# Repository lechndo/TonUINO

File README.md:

**THIS IS A FORK OF https://github.com/seisfeld/TonUINO!
unfortunately github can't handle forks of forks (with same name).**  

Alternative TonUINO Firmware
============================

Dies ist meine alternative Firmware für das wundervolle [TonUINO](https://www.voss.earth/tonuino/) Projekt. Ziel ist hier nicht unbedingt 100%ige Funktionsgleichheit mit der original Firmware. Es wurden vielmehr für meinen Zweck interessante Funktionen hinzugefügt und desweiteren auch einige Punkte (erstmal?) ausgelassen. Im großen und ganzen macht es einfach Spaß, sich mit der TonUINO Plattform auszutoben, ich bin deswegen auch viel in der [TonUINO Community](https://discourse.voss.earth/) aktiv. Schaut doch einfach mal vorbei - ihr findet dort viele Bauvorschläge, Hacks und Informationen rund um den TonUINO.

**Die Firmware wird "as-is" zur Verfügung gestellt. Wenn jemand die Firmware in seinem TonUINO einsetzt, freue ich mich natürlich darüber. Ich kann allerdings keinen Support bieten.**

## Inhalt
- [Funktionsübersicht](https://github.com/seisfeld/TonUINO#funktionsübersicht)
- [Tastenbelegung](https://github.com/seisfeld/TonUINO#tastenbelegung)
- [PIN Code](https://github.com/seisfeld/TonUINO#pin-code)
- [Ordnerstruktur auf der SD Karte](https://github.com/seisfeld/TonUINO#ordnerstruktur-auf-der-sd-karte)
- [Audio Meldungen](https://github.com/seisfeld/TonUINO#audio-meldungen)
  - [Audio Meldungen herunterladen](https://github.com/seisfeld/TonUINO#audio-meldungen-herunterladen)
  - [Audio Meldungen selbst erzeugen](https://github.com/seisfeld/TonUINO#audio-meldungen-selbst-erzeugen)
      - [Audio Meldungen mit say und ffmpeg erzeugen](https://github.com/seisfeld/TonUINO#audio-meldungen-mit-say-und-ffmpeg-erzeugen)
      - [Audio Meldungen mit Amazon Polly erzeugen](https://github.com/seisfeld/TonUINO#audio-meldungen-mit-amazon-polly-erzeugen)
      - [Audio Meldungen mit dem Cloud text-to-speech Service von Google erzeugen](https://github.com/seisfeld/TonUINO#audio-meldungen-mit-dem-cloud-text-to-speech-service-von-google-erzeugen)
      - [Hilfe und weitere Optionen](https://github.com/seisfeld/TonUINO#hilfe-und-weitere-optionen)
- [Titelansagen in MP3-Dateien einfügen](https://github.com/seisfeld/TonUINO#titelansagen-in-mp3-dateien-einfügen)
  - [Funktionsweise](https://github.com/seisfeld/TonUINO#funktionsweise)
  - [Hilfe und weitere Optionen](https://github.com/seisfeld/TonUINO#hilfe-und-weitere-optionen-1)
- [Lizenz](https://github.com/seisfeld/TonUINO#lizenz)

## Funktionsübersicht

- Standard Abspielmodi: Hörspiel, Album, Party, Lieblingsfolge und Hörbuch.
- Erweiterte Abspielmodi: Virtuelle Ordner für die Modi Hörspiel, Album und Party.
- Nächster/Vorheriger Titel sowohl in den Standard Abspielmodi Album, Party und Hörbuch - als auch bei der Nutzung von virtuellen Ordnern in den Modi Album und Party.
- Der aktuell laufende Titel kann dauerhaft wiederholt werden.
- Speichert die Ordnerverknüpfungen, Abspielmodi etc. auf den NFC Tags/Karten.
- Unterstützung für MIFARE Classic (Mini, 1K & 4K) Tags/Karten.
- Unterstützung für MIFARE Ultralight / Ultralight C Tags/Karten.
- Unterstützung für NTAG213/215/216 Tags/Karten.
- Debugausgabe auf der seriellen Konsole.
- Einstellungen werden im EEPROM gespeichert.
- Konfigurationsdialoge (NFC Tags/Karten anlernen/löschen, Elternmenü etc.) können abgebrochen werden.
- NFC Tags/Karten können wieder komplett gelöscht werden.
- Elternmenü um NFC Tags/Karten zu löschen und um Einstellungen wie Startlautstärke, Maximallautstärke, Menülautstärke, Equalizer und Abschalttimer (benötigt eine externe Schaltung oder eine passende Powerbank) vorzunehmen. Dort kann TonUINO auch von Hand abgeschaltet werden und es lassen sich der Hörbuchfortschritt und die Einstellugen zurücksetzen.
- **Optional:** PIN Code um Elternfunktionen zu schützen.
- **Optional:** Umstellbar auf 5 Tasten Bedienung.
- **Optional:** Fernbedienbar über eine Infrarotfernbedienung (diese muss mindestens 7 Tasten haben), welche über das Elternmenü angelernt werden kann. Über die Fernbedienung ist es dann auch möglich die Tasten von TonUINO zu sperren.
- **Optional:** Unterstützung einer Status LED.
- **Optional:** Unterstützung von WS281x LED(s) als Status LED(s).
- **Optional:** Unterspannungsabschaltung für z.B. die [CubieKid Platine](https://www.thingiverse.com/thing:3148200).
- **Optional:** Unterstützung des [Pololu Power Switch (LV)](https://www.pololu.com/product/2808).

## Tastenbelegung

## PIN Code

Der (optional einschaltbare) PIN Code um die Elternfunktionen abzusichern lautet standard mässig

- `play/pause, vol-, vol+, play/pause`

und kann im Sketch vor dem kompilieren geändert werden.

## Ordnerstruktur auf der SD Karte

Die Ordner auf der SD Karte, in denen eure MP3-Dateien abgelegt werden, müssen **01 bis 99** heissen - also **zweistellig** sein. Die Dateien in den Ordnern müssen mit einer **dreistelligen** Nummer beginnen - **001 bis 255** - können aber in der Regel [1] weitere Zeichen enthalten. Erlaubt wäre demnach `001.mp3` oder auch `001Lieblingslied.mp3`.

Es hat sich bewährt, die gesammte Ordnerstruktur auf dem Comupter vorzubereiten und dann in einem Rutsch auf die SD Karte zu kopieren. So wird sichergestellt, daß alle Dateien auch in der richtigen Reihenfolge sind.

[1] Nicht alle DFPlayer Mini Module akzeptieren im Dateinamen weitere Zeichen hinter der dreistelligen Nummer. Hier geht dann leider nur `001.mp3`, `002.mp3` usw.

## Audio Meldungen

TonUINO funktioniert nur korrekt, wenn ein **zur Firmware passendes** Set an Audio Meldungen auf der SD Karte vorhanden ist. Dies sind die Ordner **advert** und **mp3**.

### Audio Meldungen herunterladen

Die Audio Meldungen sind mit Amazon Polly generiert worden und können in verschiedenen Sprachen heruntergeladen werden:

- Deutsch: [audio-messages-polly-de.zip](https://seisfeld.github.io/tonuino/audio-messages-polly-de.zip)
- Englisch: [audio-messages-polly-en.zip](https://seisfeld.github.io/tonuino/audio-messages-polly-en.zip)
- Niederländisch: [audio-messages-polly-nl.zip](https://seisfeld.github.io/tonuino/audio-messages-polly-nl.zip)

Die `.zip` Datei entpacken und die Ordner **advert** und **mp3** auf die SD Karte kopieren. Fertig.

### Audio Meldungen selbst erzeugen

Das passende Set an Audio Meldungen lässt sich auch jederzeit mit dem beigelegten Python Skript `create_audio_messages.py` erzeugen. Hier sind dann auch weitere text-to-speech Engines möglich wenn ihr möchtet (siehe unten). Das Skript kann sowohl **deutsche**, **englische** als auch **niederländische** Audio Meldungen erzeugen (unterstützt wird ebenfalls **französisch**, es liegt dafür allerdings momentan keine Quelldatei bei). Es ist unter macOS, Linux und Windows getested, und benötigt **Python 3** und ggf. **ffmpeg**.

Unter Linux kann Python 3 mit dem zur Distribution gehörenden Paketmanager installiert werden. macOS Nutzer benutzen z.B. [Homebrew](https://brew.sh): `brew install python` und für Windows kann es [hier heruntergeladen werden](https://www.python.org/downloads/windows/).

Das Skript unerstützt dabei die Nutzung von drei text-to-speech Engines:

- Lokal - nur unter macOS - mit den Tools `say` und `ffmpeg`. Sofern man einen Mac hat ist dieser Weg schnell, einfach und dauerhaft kostenlos.
- Über das Internet mit Amazon Polly, dem text-to-speech Service von Amazon.
- Über das Internet mit Hilfe des Cloud text-to-speech Service von Google.

Für die Anzahl der benötigten Meldungen ist die Nutzung der Services von Amazon ([Preise](https://aws.amazon.com/de/polly/pricing/)) bzw. Google ([Preise](https://cloud.google.com/text-to-speech/pricing)) erstmal kostenlos. Für beide Services muss man allerdings erst einen Account anlegen, ist dann das Freikontingent irgendwann einmal aufgebraucht fallen Kosten im Bereich von ein paar Cent an.

#### Audio Meldungen mit `say` und `ffmpeg` erzeugen

Neben dem Tool `say` (ist Teil von macOS) wird hier noch `ffmpeg` benötigt.

1. `ffmpeg` installieren, z.B. via [Homebrew](https://brew.sh): `brew install ffmpeg`
2. In den Ordner wechseln wo ihr die `.zip` Datei von GitHub entpackt, bzw. das Repository gecloned habt.
3. `python3 tools/create_audio_messages.py --use-say` ausführen.
4. Kopiert nun den Inhalt des Ordners **sd-card** auf die SD Karte. Fertig.

#### Audio Meldungen mit Amazon Polly erzeugen

1. Auf der [AWS](https://aws.amazon.com/) Webseite einen Account anlegen und Access Keys erzeugen.
2. Das Tool `aws` [installieren](https://docs.aws.amazon.com/de_de/cli/latest/userguide/cli-chap-install.html) (Windows / Linux), macOS z.B. via [Homebrew](https://brew.sh): `brew install awscli`.
3. Das Tool `aws` [konfigurieren](https://docs.aws.amazon.com/de_de/cli/latest/userguide/cli-chap-configure.html).
4. In den Ordner wechseln wo ihr die `.zip` Datei von GitHub entpackt, bzw. das Repository gecloned habt.
5. `python3 tools/create_audio_messages.py --use-amazon` ausführen.
6. Kopiert nun den Inhalt des Ordners **sd-card** auf die SD Karte. Fertig.

#### Audio Meldungen mit dem Cloud text-to-speech Service von Google erzeugen

1. Auf Googles [Cloud text-to-speech](https://cloud.google.com/text-to-speech/) Webseite einen Account anlegen und einen API-Key erzeugen.
2. In den Ordner wechseln wo ihr die `.zip` Datei von GitHub entpackt, bzw. das Repository gecloned habt.
3. `python3 tools/create_audio_messages.py --use-google-key=ABCD` ausführen.
4. Kopiert nun den Inhalt des Ordners **sd-card** auf die SD Karte. Fertig.

#### Hilfe und weitere Optionen

Das Python Skript hat noch einige weitere Funktionen. Eine Übersicht gibt:

- `python3 tools/create_audio_messages.py --help`

## Titelansagen in MP3-Dateien einfügen

Im Hörspielmodus gibt es das Problem, daß man beim Auflegen der Karte nicht weiß, welche Folge abgespielt wird. Spielt man z.B. *Benjamin Blümchen* ab, dann kommt immer zuerst der Titelsong, der sich bei allen Folgen gleich anhört.

Das Python Skript `add_lead_in_messages.py` fügt der MP3-Datei eine Titelansage wie z.B. *Benjamin Blümchen im Urlaub* hinzu. Wenn man eine andere Folge hören möchte, kann man dann einfach nochmal die *Benjamin Blümchen* Karte auflegen. Es ist unter macOS getested, sollte aber mit minimalem Aufwand auch unter Windows / Linux laufen - wenn alle Abhängigkeiten erfüllt werden.

### Funktionsweise

Angenommen man hat einen Ordner mit folgendem Inhalt:

```
+- 04_Benjamin Blümchen
   +- Benjamin Blümchen hat Geburtstag.mp3
   +- Benjamin Blümchen im Urlaub.mp3
   +- Benjamin Blümchen als Pilot.mp3
```

Dann kann man mit folgendem Aufruf MP3-Dateien mit Ansagen generieren (Beispiel):

    python3 tools/add_lead_in_messages.py -i '04_Benjamin Blümchen' -o /Volumes/TonUINO/04 --google-key=ABCD --add-numbering

Was dann passiert:

- Es werden neue MP3-Dateien mit den Ansagen erzeugt. Man kann dabei auch optional direkt auf die SD-Karte schreiben (wie im Beispiel).
- Die Original-Dateien werden dabei nicht geändert.
- Die MP3-Dateien werden nicht neu enkodiert (also kein Qualitätsverlust).
- Auf Wunsch werden die MP3-Dateien kompatibel zum DFPlayer Mini numeriert. Also z.B. `001_Benjamin Blümchen hat Geburtstag.mp3` (Parameter `--add-numbering`)
- Das Skript unerstützt dabei die Nutzung von drei text-to-speech Engines:
  - Lokal - nur unter macOS - mit den Tools `say` und `ffmpeg`. (Parameter `--use-say`)
  - Über das Internet mit Amazon Polly, dem text-to-speech Service von Amazon. (Parameter `--use-amazon`)
  - Über das Internet mit Hilfe des Cloud text-to-speech Service von Google. (Parameter `--google-key=ABCD`)

Das Ergebnis sieht dann so aus:

```
+- /Volumes/TonUINO/04
   +- 001_Benjamin Blümchen hat Geburtstag.mp3
   +- 002_Benjamin Blümchen im Urlaub.mp3
   +- 003_Benjamin Blümchen als Pilot.mp3
```

#### Hilfe und weitere Optionen

Das Python Skript hat noch einige weitere Funktionen. Eine Übersicht gibt:

- `python3 tools/add_lead_in_messages.py --help`

## Lizenz

GPL v3. Siehe [LICENSE](../LICENSE.md).

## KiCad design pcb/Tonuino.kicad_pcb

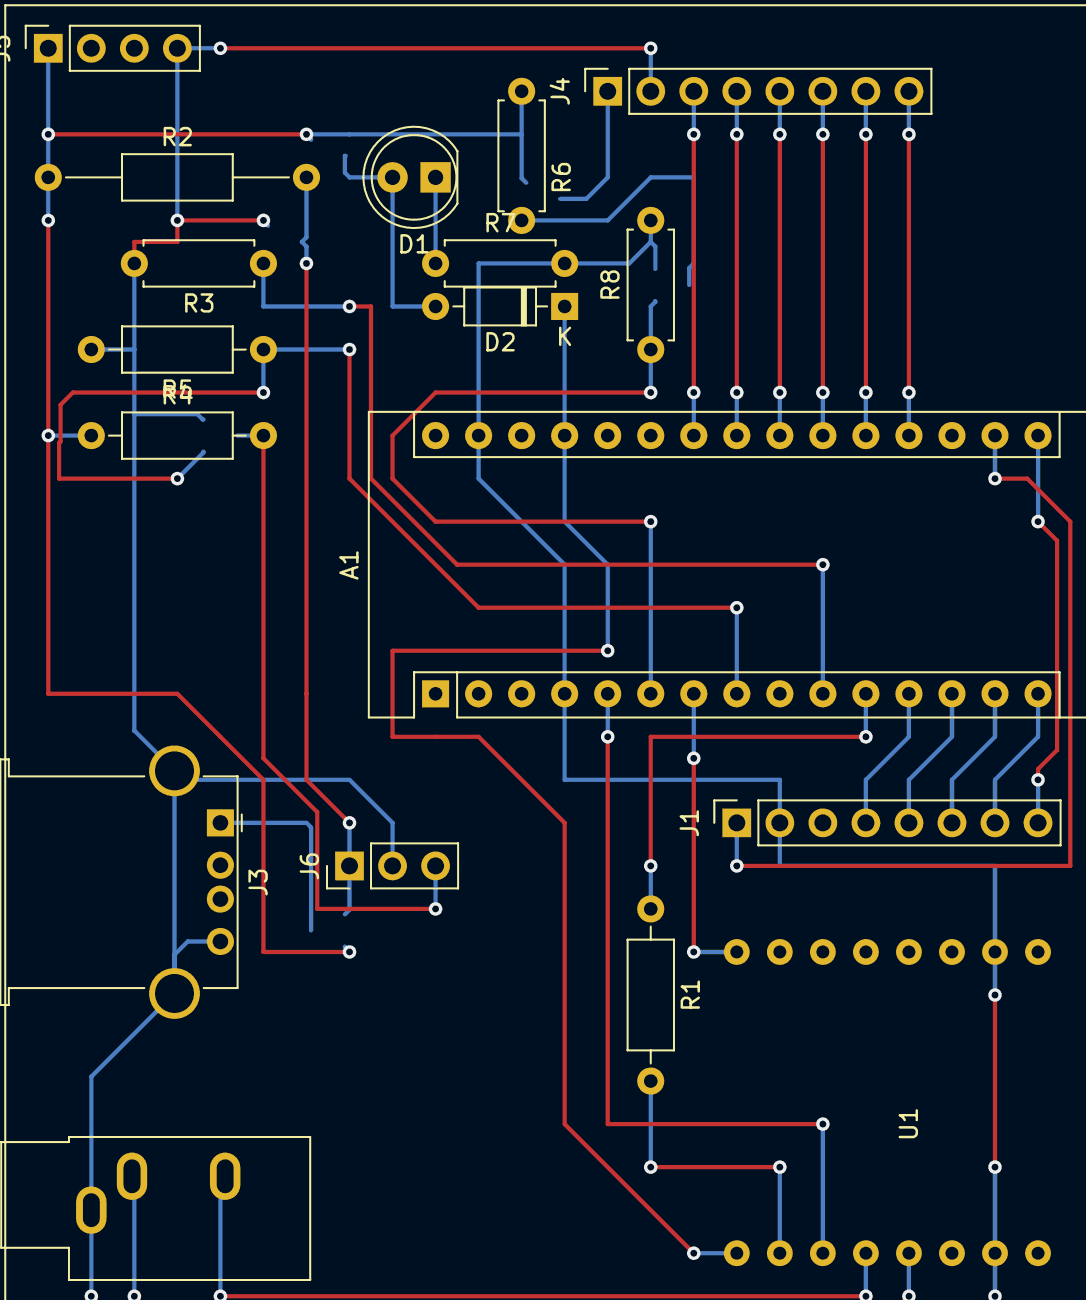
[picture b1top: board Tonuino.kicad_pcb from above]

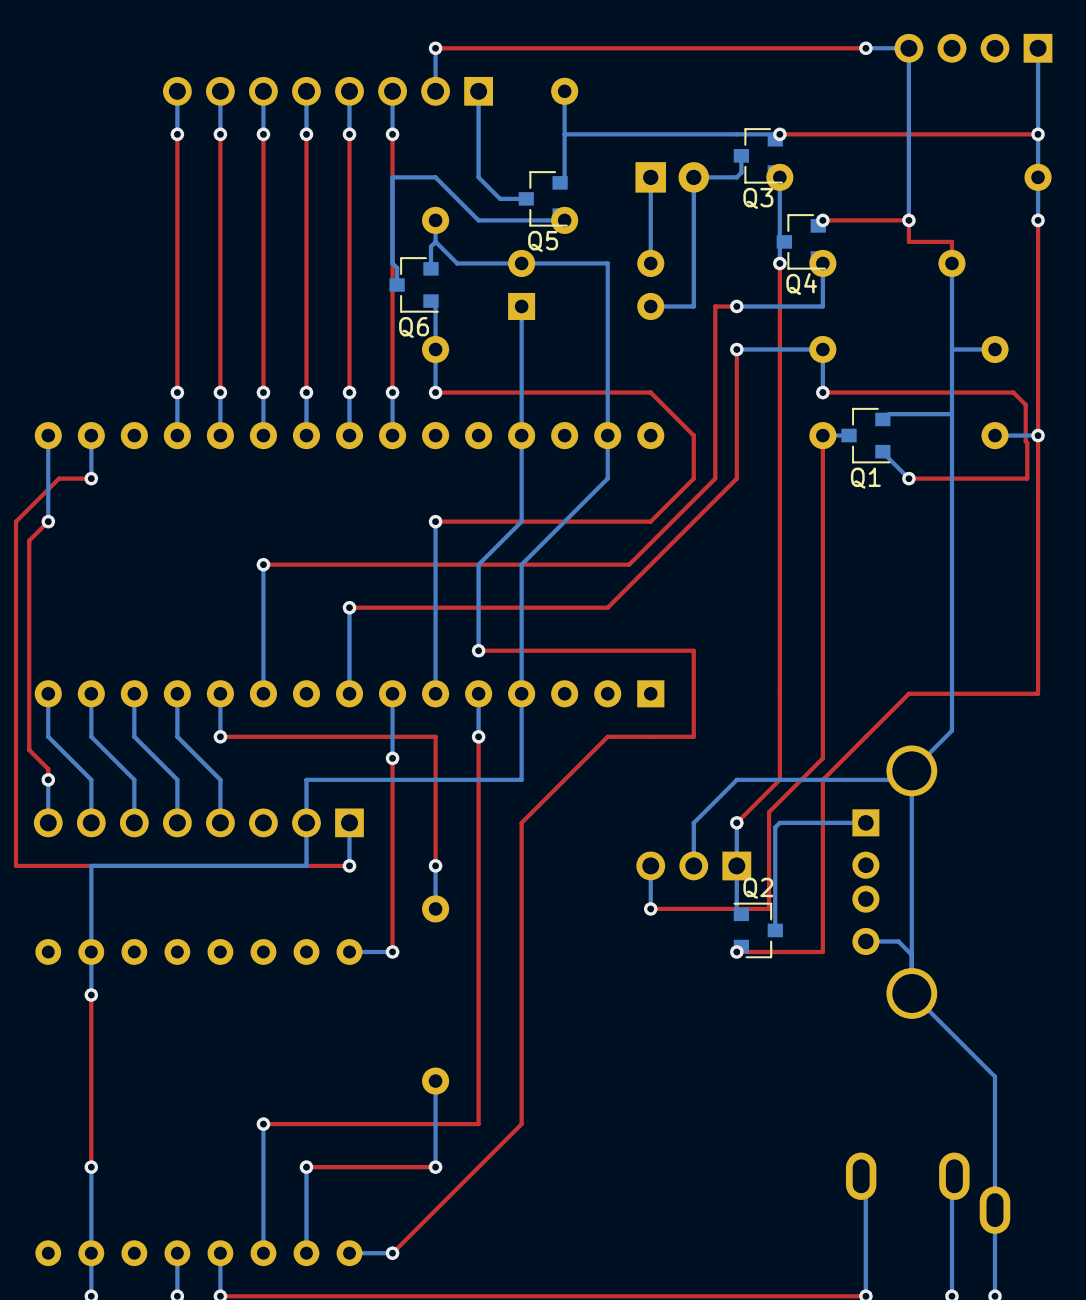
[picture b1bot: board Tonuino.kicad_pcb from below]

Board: 2 copper layers, 24 parts (6 on the bottom side), 31 nets.

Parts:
A1: Arduino_Nano_v2.x; Arduino_Nano
D1: LED; LED_D5.0mm
D2: 1N5817; D_DO-35_SOD27_P7.62mm_Horizontal
J1: ConRFID; PinSocket_1x08_P2.54mm_Vertical
J2: AudioJack3; Jack_3.5mm_CUI_SJ1-3533NG_Horizontal
J3: USB_A; USB_A_Stewart_SS-52100-001_Horizontal
J4: ConButtons; PinSocket_1x08_P2.54mm_Vertical
J5: ConInput; PinSocket_1x04_P2.54mm_Vertical
J6: Conn_01x03_Female; PinHeader_1x03_P2.54mm_Vertical
Q1, Q4, Q6: IRLML2060; SOT-23
Q2, Q3, Q5: IRLML6402; SOT-23
R1: 1k; R_Axial_DIN0207_L6.3mm_D2.5mm_P10.16mm_Horizontal
R2: 650k; R_Axial_DIN0207_L6.3mm_D2.5mm_P15.24mm_Horizontal
R3: 650k; R_Axial_DIN0207_L6.3mm_D2.5mm_P7.62mm_Horizontal
R4: 33R; R_Axial_DIN0207_L6.3mm_D2.5mm_P10.16mm_Horizontal
R5: 650k; R_Axial_DIN0207_L6.3mm_D2.5mm_P10.16mm_Horizontal
R6, R8: 6k34; R_Axial_DIN0207_L6.3mm_D2.5mm_P7.62mm_Horizontal
R7: 230; R_Axial_DIN0207_L6.3mm_D2.5mm_P7.62mm_Horizontal
U1: DFPLAYER_MINI; DFPlayer

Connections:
+3V3: A1.17, J1.1
+5V: A1.27, D2.1, U1.1
+BATT: J5.1, Q2.2, Q3.2, Q5.2, R2.1, R4.1, R6.1
/Btn1: A1.19, J4.8
/Btn2: A1.20, J4.7
/Btn3: A1.21, J4.6
/Btn4: A1.22, J4.5
/Btn5: A1.23, J4.4
/Btn6: A1.24, J4.3
/BtnLigth_5V0: J4.1, Q5.3
/DFP_MISO: A1.15, J1.7
/DFP_MOSI: A1.14, J1.6
/DFP_RST: A1.12, J1.4
/DFP_SCK: A1.16, J1.8
/DFP_SDA(SS): A1.13, J1.5
GND: A1.4, A1.29, J1.2, J2.S, J3.4, J3.5, J4.2, J5.4, J6.2, Q1.2, Q4.2, Q6.2, R3.2, R5.2, R7.2, R8.2, U1.7, U1.10
unnamed: A1.5, U1.3
unnamed: A1.7, U1.16
unnamed: D1.1, R7.1
unnamed: D1.2, D2.2, Q3.3
unnamed: J3.1, Q2.3
unnamed: Q5.1, Q6.3, R6.2
unnamed: R1.2, U1.2
PIN_ALIVE: A1.8, Q1.1, R5.1
PIN_AUDIO_LEFT: J2.T, U1.5
PIN_AUDIO_RIGHT: J2.R, U1.4
PIN_BTN_PWM: A1.6, Q6.1, R8.1
PIN_DF_RX: A1.11, R1.1
PIN_PWR_ON: A1.10, Q4.1, R3.1
SW_ALIVE: J6.3, Q1.3, R4.2
SW_PWR_ON: J6.1, Q2.1, Q3.1, Q4.3, R2.2

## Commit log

2019-07-29 Added boundary for jump back in special play modes
    Added boundary for jump back in special play modes, as mentioned by stockf in #37
    https://github.com/xfjx/TonUINO/issues/37
2019-07-29 Changed code style
    The changes already save ~800 bytes (3% on a nano) and several cycles.
2019-07-29 Changed card read/write, volume functions
    Replaced multiple write/read commands with a loop.
    Changed volume increase/decrease functions.
    Saving ~1.2k (4% on a nano).
2019-07-31 Added sub menu constants
2019-07-31 Added boundary for jump back in special play modes
    Added boundary for jump back in special play modes, as mentioned by stockf in #37
    https://github.com/xfjx/TonUINO/issues/37
2019-07-31 Fixed typo
2019-09-07 Final version of customized Tonuino.
    Most of the #ifdefs were removed and software is modified according to my requirements.
    Some of the Serial.prints() were removed to free some more memory.
2019-09-08 Implemented simple "LearnToCalculate" modifier mode (#7). Allows for creation of modifier cards for addition, subtraction, multiplication, division or mixed calculations. When activating the modifier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
    Added MP3 files 0410 to 0429 and 0977.
2019-09-08 changed handling of old rfid cards.
2019-09-22 Added LearnToCalculate Modifier.
    Added persistent modifiers.
    Fixed overwriting of cards if multiple card were stacked (implemented Card UID compare).
    Removed several Serial.print to get more space.
2019-09-25 Fixed some wrong MP3/ADV associations.
    Added sleep timer minute anouncement.
2019-11-11 Copied contents from seisfeld fork
    Copied contents from https://github.com/seisfeld/TonUINO/blob/master/tonuino.ino, cause github can not handle forks of forks (with same name).
2019-11-17 Preliminary pc mode for seisfeld
2020-01-25 PCB: add gitignore file for kicad project
2020-01-25 PCB: Add git submodules for kicad libraries
2020-01-25 PCB: initial commit for schematic and layout
    The schematic is quit messy because of several changes being
    made while soldering the PCB and doing some tests with my
    USB powerbank.
    The layout was made for soldering everything onto a
    breadboard and is a try to get a more or less planar layout.
2020-01-25 Adapted gitignore for Eclipse and vi files
2020-01-25 Add symlink Tonuino.cpp to Tonuino.ino
    for simple editing and compiling under Eclipse.
2020-01-25 Remove status LED code because I don't have one.
    Maybe it would have been better to keep the code and
    just instead add a compile time switch to disable it...
2020-01-25 Add includes and forward declarations
    to satisfy compilers and IDEs that don't do this
    automatically (like Adruino IDE or platform IO).
2020-01-25 Add platform config file and replace reset pin
    (because I don't have one) by checking for common press of buttons
    pause, up and down on startup.
2020-01-25 Adapt code for power switch circuit handling
2020-01-26 Add USB power bank keep-alive-module
    which is required to regularly trigger a circuit that
    consumes more current for a short time to ensure the
    power bank doesn't shut down.
2020-01-26 Add initial button LED PWM handling
    setting a default value.
    To be extended to adapt PWM value according to surrounding light
    intensity measured with OPT101 module.
2020-01-26 Add MP3 intro sound file
2020-01-26 Add button combination for instant shutdown
    by pressing UP and DOWN buttons for VERY_LONG_PRESS ms
    which is configurable via define in platformConfig.h
2020-01-26 Trying to backport five-button mode support
    to be able to have volume buttons separate.
